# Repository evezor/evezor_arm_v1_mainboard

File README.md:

# evezor_arm_v1_mainboard_v1

This baord is based on the RAMPS1.4 Board https://reprap.org/wiki/RAMPS_1.4

The motor connectors have been changed to Molex KK connectors and the extra pins are broken out in the Gadgeteer Standard pinout

Source files can be found here: https://github.com/evezor/evezor_arm_v1_mainboard_V1

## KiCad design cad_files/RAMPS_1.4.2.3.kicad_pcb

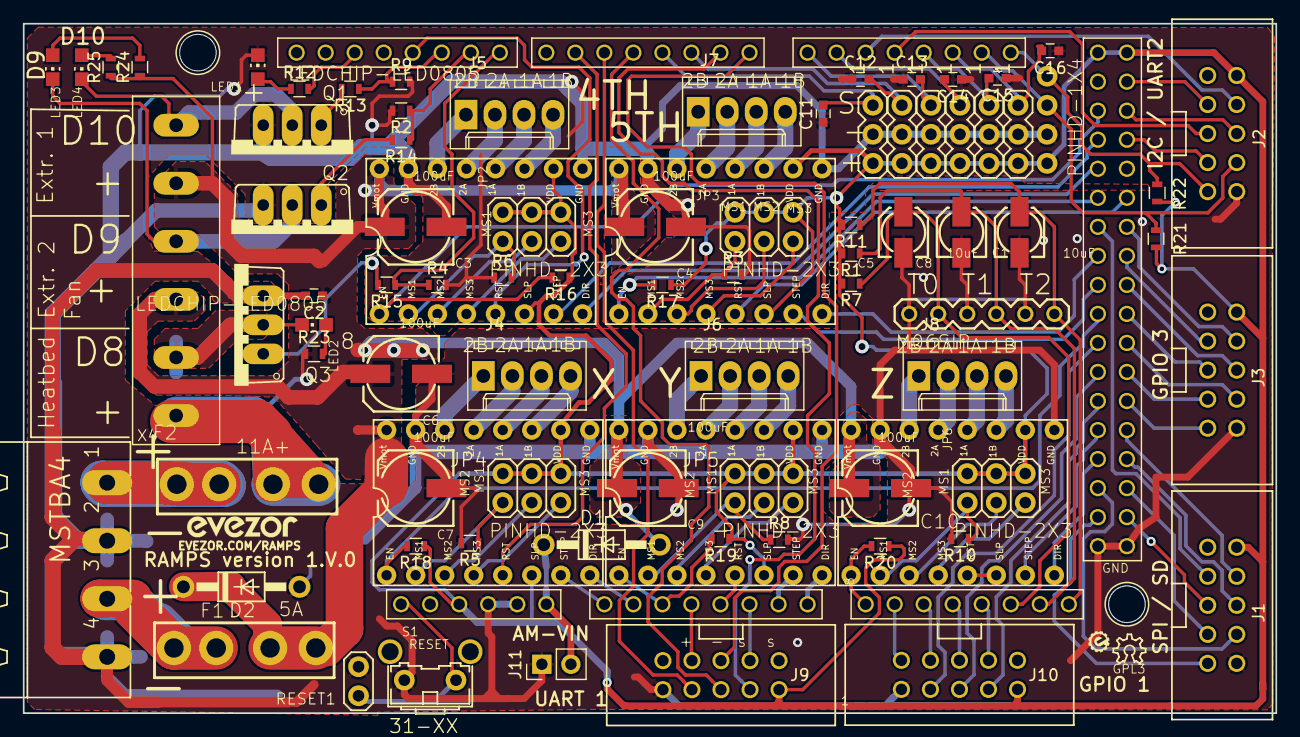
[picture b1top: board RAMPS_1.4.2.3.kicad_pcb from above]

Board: 2 copper layers, 109.6 x 60.3 mm, 87 parts (0 on the bottom side), 119 nets.

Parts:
C1, C5, C8: 10uF; 153CLV-0405
C2: 100nF; C_0603
C3, C4, C6, C7, C9, C10: 100uF; 153CLV-0605
C11, C12, C13, C14, C15, C16: C-EUC0805; C_0603
D1, D2: 1N4004; DO41-10
F1, F2: FUSE_MCCQ-122
I2C1: PINHD-1X4; 1X04
J1, J2, J3, J9, J10: Conn_02x05_Odd_Even; 10_PIN_IDC
J4, J5, J6, J7, J8: Conn_01x04; Molex_KK-6410-04_04x2.54mm_Straight
J11: Conn_01x02; Pin_Header_Straight_1x02_Pitch2.54mm
JP2, JP3, JP4, JP5, JP6: PINHD-2X3; 2X03
JP7: M06SIP; 1X06
LED1, LED2, LED3, LED4: LEDCHIP-LED0805; CHIP-LED0805
LOGO1: OSHW_LOGO_6MILX0100-NT; OSHW_6X100_NOTEXT
Q1, Q2, Q3: STP55NF06L; TO220BV
R1, R7, R11, R21, R22: 4.7K; R_0603
R2, R3, R4, R5, R6, R8, R9, R10: 100k; R_0603
R12: 1K; R_0603
R13, R14, R15: 10r; R_0603
R16, R17, R18, R19, R20: 10k; R_0603
R23, R24, R25: 1.8K; R_0603
RESET1: PINHD-2
S1: 31-XX; B3F-31XX
U1: ARDUINO_MEGA_SHIELD
U$2: 282837-6
U$4, U$5, U$6, U$7, U$8: A4988BREAKOUT
X4: MSTBA4
X+1: 3PIN-HEADER
X-1: 3PIN-HEADER
Y+1: 3PIN-HEADER
Y-1: 3PIN-HEADER
Z+1: 3PIN-HEADER
Z-1: 3PIN-HEADER

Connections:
+12V: C2.1, C3.+, C4.+, C6.+, C7.+, C9.+, C10.+, D1.A, D2.C, F1.2-1, F1.2-2, F2.2-1, F2.2-2, R23.1, R24.1, R25.1, U$2.P$1, U$2.P$3, U$2.P$5, U$4.VMOT, U$5.VMOT, U$6.VMOT, U$7.VMOT, U$8.VMOT
A3: J9.7, U1.A3
A4: U1.A4, U$7.RST
A5: J9.3, U1.A5
A9: J10.9, U1.A9
A10: J10.7, U1.A10
A11: J10.5, U1.A11
A12: J10.3, U1.A12
AM-VIN: D1.C, J11.2, U1.VIN
D1: J9.5, U1.RX
D2: J9.4, U1.TX
D4: J9.6, U1.D4
D5: J9.8, U1.D5
D6: U1.D6, U$6.RST
D8: R4.1, R15.1, U1.D8
D9: R2.1, R14.1, U1.D9
D10: R9.1, R13.1, U1.D10
D11: U1.D11, U$4.RST
D16: J2.4, U1.D16
D17: J2.5, U1.D17
D23: J2.3, U1.D23
D25: J2.6, U1.D25
D27: J2.7, U1.D27
D31: U1.D31, U$5.RST
D32: J1.3, U1.D32
D33: J3.4, U1.D33
D35: J3.3, U1.D35
D37: J3.6, U1.D37
D39: J3.5, U1.D39
D40: J10.8, U1.D40
D41: J3.8, U1.D41
D42: J10.6, U1.D42
D43: J3.7, U1.D43
D44: J10.4, U1.D44
D45: J3.9, U1.D45
D47: J1.4, U1.D47
D49: J1.6, U1.D49
D53: J1.5, U1.D53
E0-DIR: U1.D28, U$4.DIR
E0-EN: R16.2, U1.D24, U$4.EN
E0-STEP: U1.D26, U$4.STEP
E1-DIR: U1.D34, U$5.DIR
E1-EN: R17.2, U1.D30, U$5.EN
E1-STEP: U1.D36, U$5.STEP
GND: C1.-, C2.2, C3.-, C4.-, C5.-, C6.-, C7.-, C8.-, C9.-, C10.-, C11.1, C12.1, C13.1, C14.1, C15.1, C16.1, D2.A, I2C1.2, J1.10, J2.10, J3.10, J9.10, J10.10, J11.1, JP7.1, JP7.3, JP7.5, LED1.C, Q1.S, Q2.S, Q3.S, R2.2, R3.2, R4.2, R5.2, R6.1, R8.2, R9.2, R10.2, RESET1.2, S1.1, U1.GND@0, U1.GND@1, U1.GND@3, U1.GND@4, U$4.GND, U$4.GND@0, U$5.GND, U$5.GND@0, U$6.GND, U$6.GND@0, U$7.GND, U$7.GND@0, U$8.GND, U$8.GND@0, X4.2, X4.4, X+1.2, X-1.2, Y+1.2, Y-1.2, Z+1.2, Z-1.2
LED: R12.2, U1.D13
MISO: J1.8, U1.D50
MOSI: J1.7, U1.D51
unnamed: LED3.C, Q2.D, U$2.P$4
unnamed: JP2.1, R6.2, U$4.MS1
unnamed: JP2.5, U$4.MS3
unnamed: LED4.C, Q1.D, U$2.P$6
unnamed: JP2.3, U$4.MS2
unnamed: JP4.1, R5.1, U$6.MS1
unnamed: JP4.3, U$6.MS2
unnamed: JP5.3, U$7.MS2
unnamed: JP4.5, U$6.MS3
unnamed: JP3.1, R3.1, U$5.MS1
unnamed: JP5.5, U$7.MS3
unnamed: LED2.A, R23.2
unnamed: JP5.1, R8.1, U$7.MS1
unnamed: JP3.5, U$5.MS3
unnamed: JP3.3, U$5.MS2
unnamed: JP6.3, U$8.MS2
unnamed: U$8.RST, U$8.SLP
unnamed: JP6.5, U$8.MS3
unnamed: JP6.1, R10.1, U$8.MS1
unnamed: LED3.A, R24.2
unnamed: LED1.A, R12.1
unnamed: Q2.G, R14.2
unnamed: Q1.G, R13.2
unnamed: Q3.G, R15.2
unnamed: LED4.A, R25.2
unnamed: LED2.C, Q3.D, U$2.P$2
unnamed: F2.1-1, F2.1-2, X4.1
unnamed: F1.1-1, F1.1-2, X4.3
unnamed: J4.1, U$6.2B
unnamed: J4.2, U$6.2A
unnamed: J4.3, U$6.1A
unnamed: J4.4, U$6.1B
unnamed: J5.1, U$4.2B
unnamed: J5.2, U$4.2A
unnamed: J5.3, U$4.1A
unnamed: J5.4, U$4.1B
unnamed: J6.1, U$7.2B
unnamed: J6.2, U$7.2A
unnamed: J6.3, U$7.1A
unnamed: J6.4, U$7.1B
unnamed: J7.1, U$5.2B
unnamed: J7.2, U$5.2A
unnamed: J7.3, U$5.1A
unnamed: J7.4, U$5.1B
unnamed: J8.1, U$8.2B
unnamed: J8.2, U$8.2A
unnamed: J8.3, U$8.1A
unnamed: J8.4, U$8.1B
RESET: RESET1.1, S1.2, U1.RES
SCK: J1.9, U1.D52
SCL: I2C1.4, J2.9, R22.1, U1.D21
SDA: I2C1.3, J2.8, R21.1, U1.D20
THERM0: C5.+, JP7.2, R7.1, U1.A13
THERM1: C8.+, JP7.4, R1.1, U1.A14
THERM2: C1.+, JP7.6, R11.1, U1.A15
VCC: I2C1.1, J1.2, J2.2, J3.2, J9.2, J10.2, JP2.2, JP2.4, JP2.6, JP3.2, JP3.4, JP3.6, JP4.2, JP4.4, JP4.6, JP5.2, JP5.4, JP5.6, JP6.2, JP6.4, JP6.6, R1.2, R7.2, R11.2, R16.1, R17.1, R18.1, R19.1, R20.1, R21.2, R22.2, U1.5V@0, U1.5V@1, U1.5V@2, U$4.SLP, U$4.VDD, U$5.SLP, U$5.VDD, U$6.SLP, U$6.VDD, U$7.SLP, U$7.VDD, U$8.VDD, X+1.3, X-1.3, Y+1.3, Y-1.3, Z+1.3, Z-1.3
X-DIR: U1.A1, U$6.DIR
X-EN: R18.2, U1.D38, U$6.EN
X-MAX: C12.2, U1.D2, X+1.1
X-MIN: C11.2, U1.D3, X-1.1
X-STEP: U1.A0, U$6.STEP
Y-DIR: U1.A7, U$7.DIR
Y-EN: R19.2, U1.A2, U$7.EN
Y-MAX: C14.2, U1.D15, Y+1.1
Y-MIN: C13.2, U1.D14, Y-1.1
Y-STEP: U1.A6, U$7.STEP
Z-DIR: U1.D48, U$8.DIR
Z-EN: R20.2, U1.A8, U$8.EN
Z-MAX: C16.2, U1.D19, Z+1.1
Z-MIN: C15.2, U1.D18, Z-1.1
Z-STEP: U1.D46, U$8.STEP

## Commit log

2023-10-06 init

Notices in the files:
cad_files/RAMPS_1.4.2.3.kicad_pcb:
GPL3
GPL v3
Copyright 2011 Johnny Russell - UltiMachine
